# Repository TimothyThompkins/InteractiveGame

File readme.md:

## Description

This is a work in progress, but ultimately aspires to a space invaders-esque game which is played completely on an embedded touch controller and interfaced with a display device such as a computer, or Rasbery Pi.

### Current revision of the PCB:

### The unpopulated (left) and populated (right) boards:

### Loading screen for the game, developed in python:

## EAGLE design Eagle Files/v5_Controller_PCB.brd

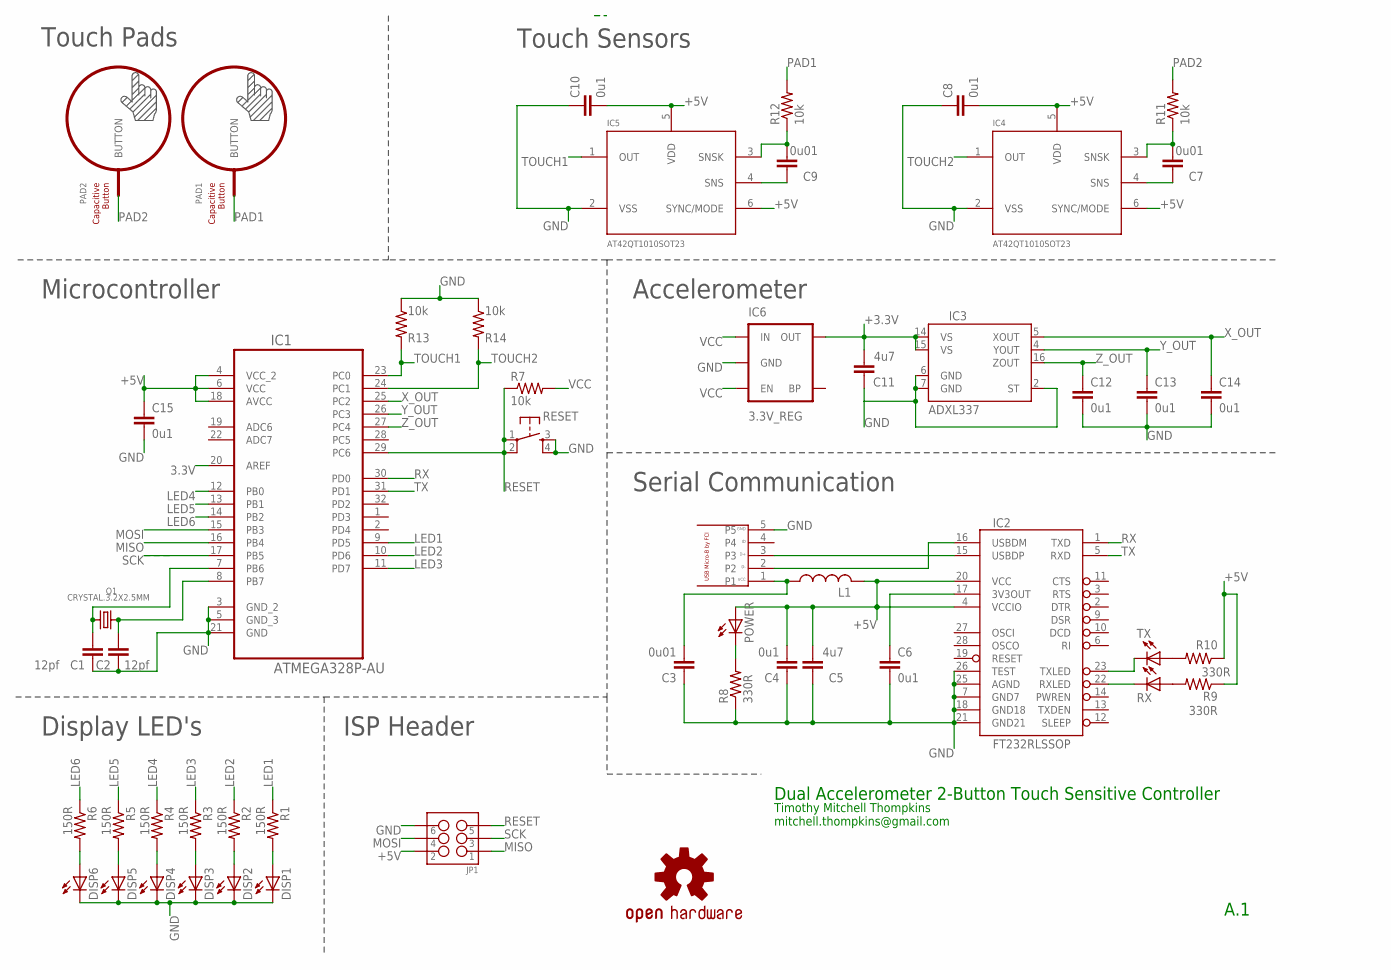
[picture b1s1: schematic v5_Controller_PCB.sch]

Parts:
BUTTON1: TOUCH_LOGO
C1, C2: 12pf; C0603
C3, C7, C9: 0u01; C0603
C4, C6, C8, C10, C12, C13, C14, C15: 0u1; C0603
C5, C11: 4u7; C0603
DISP1, DISP2, DISP3, DISP4, DISP5, DISP6: LEDCHIPLED_0603; CHIPLED_0603
IC1: ATMEGA328P-AU; QFP80P900X900X120-32N
IC2: FT232RLSSOP; SSOP28DB
IC3: ADXL337; LFCSP_LQ-16
IC4, IC5: AT42QT1010SOT23; SOT23-6
IC6: 3.3V_REG; SOT23-5
JP1: M03X2POGO_PINS; 2X3_POGO
L1: L-USL2012C; L2012C
LOGO2: OSHW-LOGOS; OSHW-LOGO-S
PAD1, PAD2: BUTTON_PASSIVE8MM; BUTTON_PASSIVE_8MM
POWER: LEDCHIPLED_0603; CHIPLED_0603
Q1: CRYSTAL.3.2X2.5MM; 3.2X2.5MM
R1, R2, R3, R4, R5, R6: 150R; 0603-RES
R7, R11, R12, R13, R14: 10k; 0603-RES
R8, R9, R10: 330R; 0603-RES
RESET: RESET; TACTILE_SWITCH_SMD
RX: LEDCHIPLED_0603; CHIPLED_0603
TX: LEDCHIPLED_0603; CHIPLED_0603
U$1: USB_MICRO_B_FCI; 10118194-0001LF
U$6: TOUCH_LOGO

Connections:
3.3V: IC1.20 (AREF)
+3.3V: C11.2, IC3.14 (VS), IC3.15 (VS), IC6.5 (OUT)
+5V: C4.2, C5.2, C8.2, C10.2, C15.1, IC1.4 (VCC_2), IC1.6 (VCC), IC1.18 (AVCC), IC2.4 (VCCIO), IC2.20 (VCC), IC4.5 (VDD), IC4.6 (SYNC/MODE), IC5.5 (VDD), IC5.6 (SYNC/MODE), JP1.P$2 (2), L1.2, POWER.A, R9.1, R10.1
GND: C1.1, C2.1, C3.1, C4.1, C5.1, C6.2, C8.1, C10.1, C11.1, C15.2, DISP1.C, DISP2.C, DISP3.C, DISP4.C, DISP5.C, DISP6.C, IC1.3 (GND_2), IC1.5 (GND_3), IC1.21 (GND), IC2.7 (GND7), IC2.18 (GND18), IC2.21 (GND21), IC2.25 (AGND), IC2.26 (TEST), IC3.2 (ST), IC3.6 (GND), IC3.7 (GND), IC4.2 (VSS), IC5.2 (VSS), IC6.2 (GND), JP1.P$6 (6), Q1.2 (GND), Q1.4 (GND), R8.1, R13.1, R14.1, RESET.3, RESET.4, U$1.5, U$1.GND@1 (GND), U$1.GND@2 (GND), U$1.GND@3 (GND), U$1.GND@4 (GND)
LED1: IC1.9 (PD5), R1.1
LED2: IC1.10 (PD6), R2.1
LED3: IC1.11 (PD7), R3.1
LED4: IC1.12 (PB0), R4.1
LED5: IC1.13 (PB1), R5.1
LED6: IC1.14 (PB2), R6.1
MISO: IC1.16 (PB4), JP1.P$1 (1)
MOSI: IC1.15 (PB3), JP1.P$4 (4)
unnamed: C9.2, IC5.3 (SNSK), R12.1
unnamed: C3.2, L1.1, U$1.1
unnamed: C2.2, IC1.8 (PB7), Q1.3
unnamed: C9.1, IC5.4 (SNS)
unnamed: POWER.C, R8.2
unnamed: C1.2, IC1.7 (PB6), Q1.1
unnamed: R10.2, TX.A
unnamed: C6.1, IC2.17 (3V3OUT)
unnamed: R9.2, RX.A
unnamed: IC2.16 (USBDM), U$1.2
unnamed: IC2.15 (USBDP), U$1.3
unnamed: IC2.23 (TXLED), TX.C
unnamed: IC2.22 (RXLED), RX.C
unnamed: C12.2, C13.2, C14.2
unnamed: C7.1, IC4.4 (SNS)
unnamed: C7.2, IC4.3 (SNSK), R11.1
unnamed: DISP1.A, R1.2
unnamed: DISP2.A, R2.2
unnamed: DISP3.A, R3.2
unnamed: DISP4.A, R4.2
unnamed: DISP5.A, R5.2
unnamed: DISP6.A, R6.2
PAD1: PAD1.P$1, R12.2
PAD2: PAD2.P$1, R11.2
RESET: IC1.29 (PC6), JP1.P$5 (5), R7.1, RESET.1, RESET.2
RX: IC1.30 (PD0), IC2.1 (TXD)
SCK: IC1.17 (PB5), JP1.P$3 (3)
TOUCH1: IC1.23 (PC0), IC5.1 (OUT), R13.2
TOUCH2: IC1.24 (PC1), IC4.1 (OUT), R14.2
TX: IC1.31 (PD1), IC2.5 (RXD)
VCC: IC6.1 (IN), IC6.3 (EN), R7.2
X_OUT: C14.1, IC1.25 (PC2), IC3.5 (XOUT)
Y_OUT: C13.1, IC1.26 (PC3), IC3.4 (YOUT)
Z_OUT: C12.1, IC1.27 (PC4), IC3.16 (ZOUT)

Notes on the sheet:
Timothy Mitchell Thompkins mitchell.thompkins@gmail.com
Dual Accelerometer 2-Button Touch Sensitive Controller
A.1
ISP Header
Touch Pads
Touch Sensors
Microcontroller
Serial Communication
Display LED's
Accelerometer

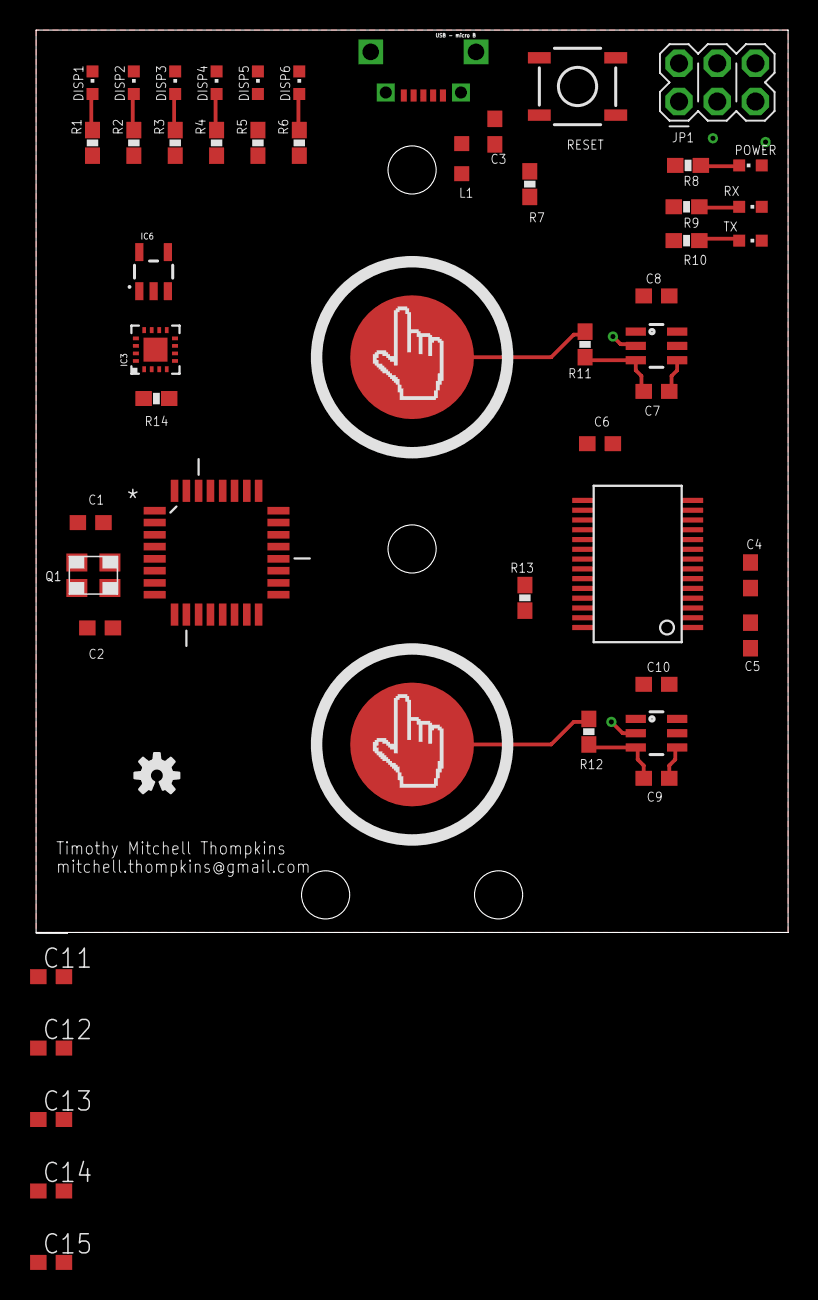
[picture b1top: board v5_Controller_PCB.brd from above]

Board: 2 copper layers, 50.0 x 60.0 mm, 54 parts (0 on the bottom side), 45 nets.

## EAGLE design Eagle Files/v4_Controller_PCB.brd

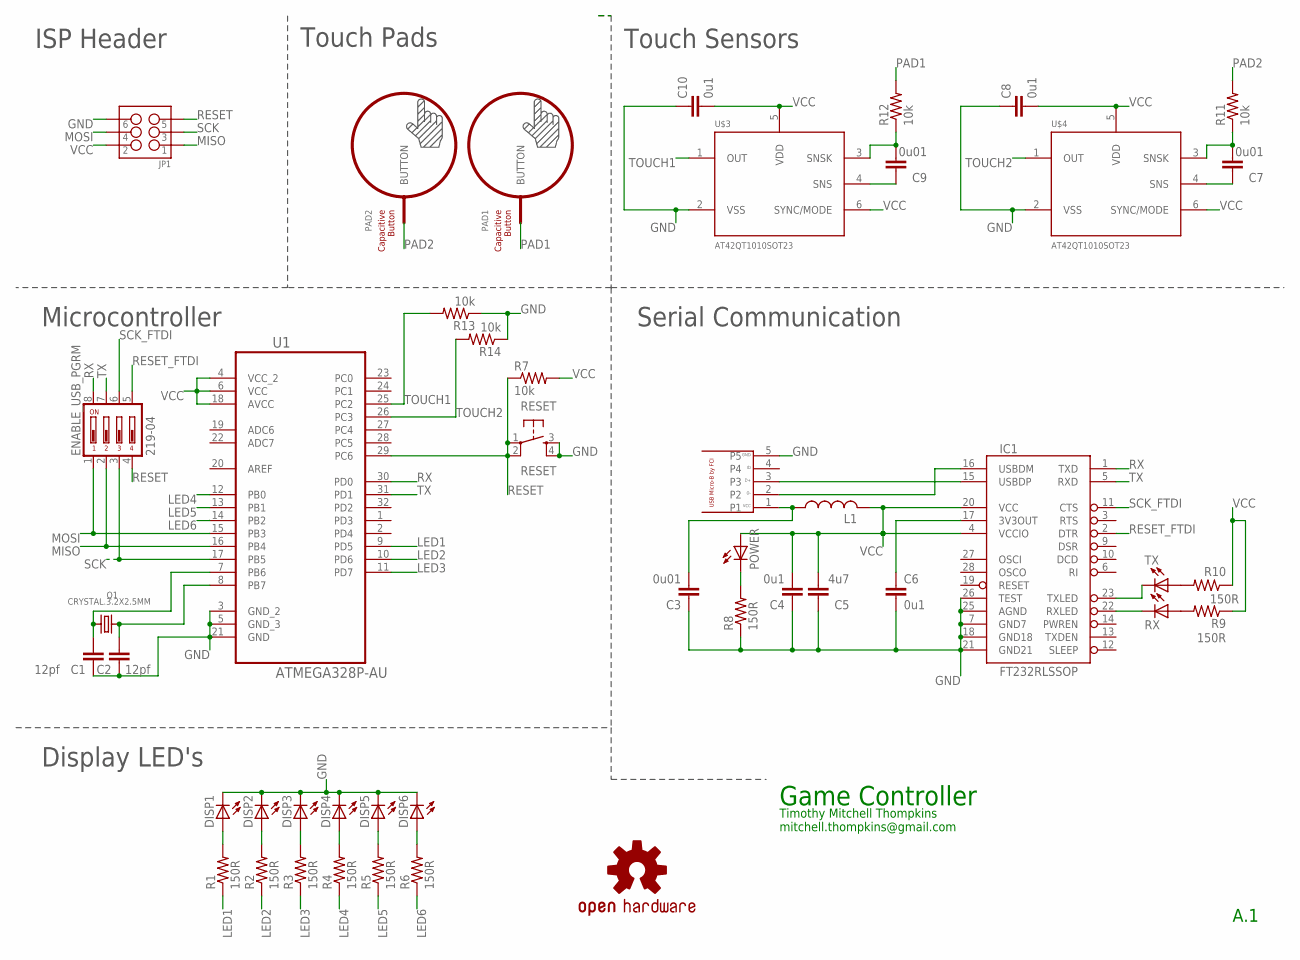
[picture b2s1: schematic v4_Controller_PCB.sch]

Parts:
BUTTON1: TOUCH_LOGO
C1, C2: 12pf; C0603
C3, C7, C9: 0u01; C0603
C4, C6, C8, C10: 0u1; C0603
C5: 4u7; C0603
DISP1, DISP2, DISP3, DISP4, DISP5, DISP6: LEDCHIPLED_0603; CHIPLED_0603
ENABLE_USB_PGRM: 219-04; CTS-219-04
IC1: FT232RLSSOP; SSOP28DB
JP1: M03X2POGO_PINS; 2X3_POGO
L1: L-USL2012C; L2012C
LOGO2: OSHW-LOGOS; OSHW-LOGO-S
PAD1, PAD2: BUTTON_PASSIVE8MM; BUTTON_PASSIVE_8MM
POWER: LEDCHIPLED_0603; CHIPLED_0603
Q1: CRYSTAL.3.2X2.5MM; 3.2X2.5MM
R1, R2, R3, R4, R5, R6, R8, R9, R10: 150R; 0603-RES
R7, R11, R12, R13, R14: 10k; 0603-RES
RESET: RESET; TACTILE-PTH
RX: LEDCHIPLED_0603; CHIPLED_0603
TX: LEDCHIPLED_0603; CHIPLED_0603
U1: ATMEGA328P-AU; QFP80P900X900X120-32N
U$1: USB_MICRO_B_FCI; 10118194-0001LF
U$3, U$4: AT42QT1010SOT23; SOT23-6
U$6: TOUCH_LOGO

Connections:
GND: C1.1, C2.1, C3.1, C4.1, C5.1, C6.2, C8.1, C10.1, DISP1.C, DISP2.C, DISP3.C, DISP4.C, DISP5.C, DISP6.C, IC1.7 (GND7), IC1.18 (GND18), IC1.21 (GND21), IC1.25 (AGND), IC1.26 (TEST), JP1.P$6 (6), Q1.2 (GND), Q1.4 (GND), R8.1, R13.1, R14.1, RESET.3, RESET.4, U1.3 (GND_2), U1.5 (GND_3), U1.21 (GND), U$1.5, U$1.GND@1 (GND), U$1.GND@2 (GND), U$1.GND@3 (GND), U$1.GND@4 (GND), U$3.2 (VSS), U$4.2 (VSS)
LED1: R1.1, U1.9 (PD5)
LED2: R2.1, U1.10 (PD6)
LED3: R3.1, U1.11 (PD7)
LED4: R4.1, U1.12 (PB0)
LED5: R5.1, U1.13 (PB1)
LED6: R6.1, U1.14 (PB2)
MISO: ENABLE_USB_PGRM.2, JP1.P$1 (1), U1.16 (PB4)
MOSI: ENABLE_USB_PGRM.1, JP1.P$4 (4), U1.15 (PB3)
unnamed: C9.2, R12.1, U$3.3 (SNSK)
unnamed: C3.2, L1.1, U$1.1
unnamed: C2.2, Q1.3, U1.8 (PB7)
unnamed: C9.1, U$3.4 (SNS)
unnamed: POWER.C, R8.2
unnamed: C1.2, Q1.1, U1.7 (PB6)
unnamed: R10.2, TX.A
unnamed: C6.1, IC1.17 (3V3OUT)
unnamed: R9.2, RX.A
unnamed: IC1.16 (USBDM), U$1.2
unnamed: IC1.15 (USBDP), U$1.3
unnamed: IC1.23 (TXLED), TX.C
unnamed: IC1.22 (RXLED), RX.C
unnamed: C7.1, U$4.4 (SNS)
unnamed: C7.2, R11.1, U$4.3 (SNSK)
unnamed: DISP1.A, R1.2
unnamed: DISP2.A, R2.2
unnamed: DISP3.A, R3.2
unnamed: DISP4.A, R4.2
unnamed: DISP5.A, R5.2
unnamed: DISP6.A, R6.2
PAD1: PAD1.P$1, R12.2
PAD2: PAD2.P$1, R11.2
RESET: ENABLE_USB_PGRM.4, JP1.P$5 (5), R7.1, RESET.1, RESET.2, U1.29 (PC6)
RESET_FTDI: ENABLE_USB_PGRM.5, IC1.2 (DTR)
RX: ENABLE_USB_PGRM.8, IC1.1 (TXD), U1.30 (PD0)
SCK: ENABLE_USB_PGRM.3, JP1.P$3 (3), U1.17 (PB5)
SCK_FTDI: ENABLE_USB_PGRM.6, IC1.11 (CTS)
TOUCH1: R13.2, U1.25 (PC2), U$3.1 (OUT)
TOUCH2: R14.2, U1.26 (PC3), U$4.1 (OUT)
TX: ENABLE_USB_PGRM.7, IC1.5 (RXD), U1.31 (PD1)
VCC: C4.2, C5.2, C8.2, C10.2, IC1.4 (VCCIO), IC1.20 (VCC), JP1.P$2 (2), L1.2, POWER.A, R7.2, R9.1, R10.1, U1.4 (VCC_2), U1.6 (VCC), U1.18 (AVCC), U$3.5 (VDD), U$3.6 (SYNC/MODE), U$4.5 (VDD), U$4.6 (SYNC/MODE)

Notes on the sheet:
Timothy Mitchell Thompkins mitchell.thompkins@gmail.com
Game Controller
A.1
ISP Header
Touch Pads
Touch Sensors
Microcontroller
Serial Communication
Display LED's

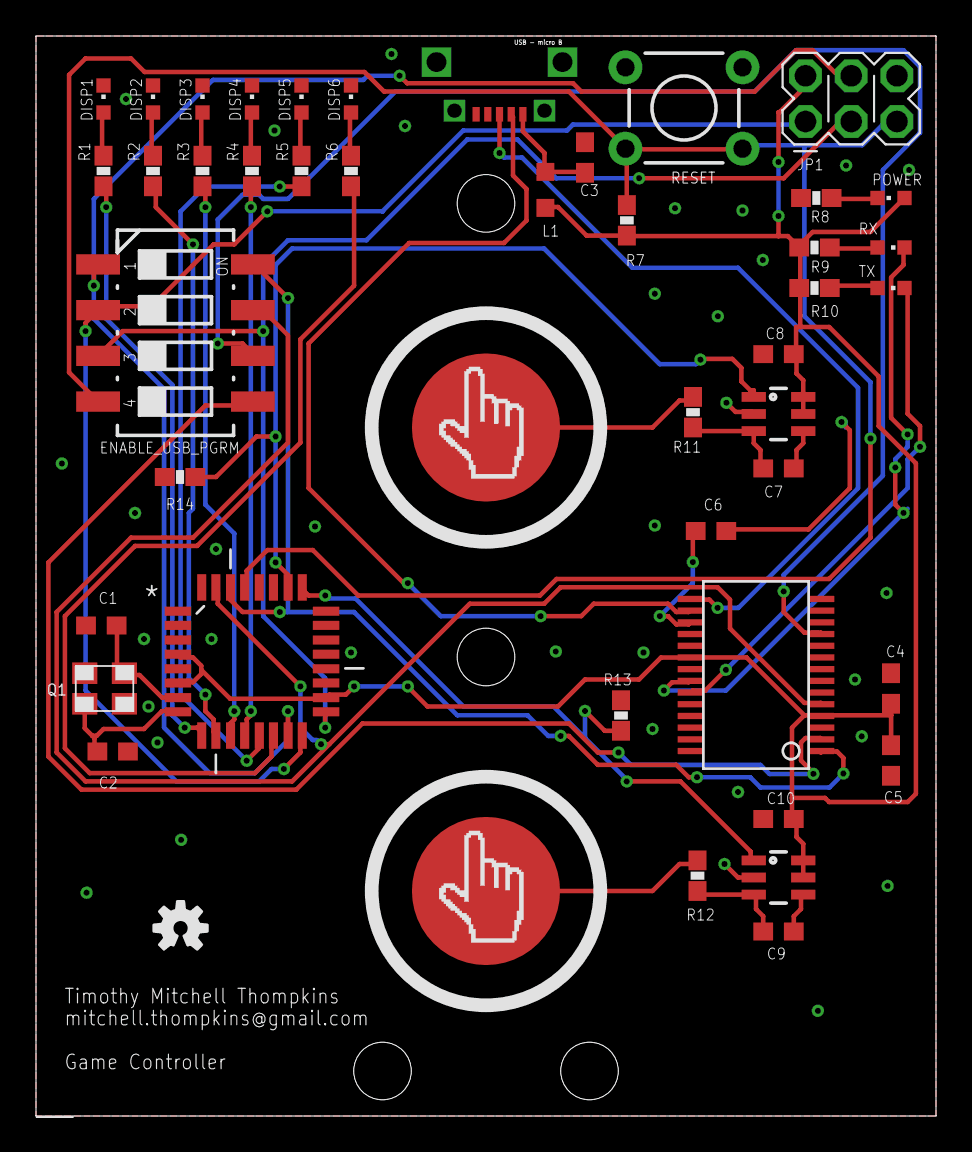
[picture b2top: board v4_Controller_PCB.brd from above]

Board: 2 copper layers, 50.0 x 60.0 mm, 48 parts (0 on the bottom side), 41 nets.

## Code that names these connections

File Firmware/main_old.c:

/*
* Hello_World.c
*
* Created: 9/28/2014 1:23:27 PM
*  Author: TimothyThompkins
*/

#define F_CPU 20000000UL // 20MHz

#include <avr/delay.h>
#include <avr/io.h>
#include <avr/interrupt.h>

#define 	UCSRA 	UCSR0A
#define 	UCSRB 	UCSR0B
#define 	UCSRC 	UCSR0C
#define 	UBRRH 	UBRR0H
#define 	UBRRL 	UBRR0L
#define 	UDRE 	UDRE0
#define 	UDR 		UDR0
#define 	RXC 		RXC0
#define TXEN		TXEN0
#define RXEN		RXEN0
#define RXCIE	RXCIE0

// Define baud rate
#define USART_BAUDRATE 9600
#define BAUD_PRESCALE (((F_CPU / (USART_BAUDRATE * 16UL))) - 1)

// Define baud rate 9600 is a safe speed as it is fast enough for most things we will use this speed
#define USART_BAUDRATE 9600

// Define the prescaler to use. This is based on the clock speed the AVR is running
#define BAUD_PRESCALE (((F_CPU / (USART_BAUDRATE * 16UL))) - 1)

void USART_Init(void){
	/*
	First set the BAUD rate, because this register is actually more than 8 bits
	we need to load the lower 8 bits and upper 8 bits independently from one another.
	We will load the lower 8 bits first and upper 8 bits after.
	Also the default frame format is 8 data bits, no parity and 1 stopbit (also known as 8n1))
	We will use this format so no change needed here
	*/
	UBRRL = BAUD_PRESCALE; // Load lower 8 bits
	UBRRH = (BAUD_PRESCALE >> 8); // Load upper 8 bits
	// Enable transmitter only
	// UCSRB = 1<<TXEN;
	UCSRB =(1<<RXEN0)|(1<<TXEN0);

}

void USART_SendByte(uint8_t data){

	// Wait until last byte has been transmitted
	while((UCSRA &(1<<UDRE)) == 0);

	// Transmit data
	UDR = data;
}

USART_ReceiveByte(){
	while ((UCSRA & (1 << RXC)) == 0);
	// Do nothing until data has been received and is ready to be read from UDR
	return(UDR); // return the byte
}

//volatile unsigned char value;
/* This variable is volatile so both main and RX interrupt can use it.
It could also be a uint8_t type */

/* Interrupt Service Routine for Receive Complete
NOTE: vector name changes with different AVRs see AVRStudio -
Help - AVR-Libc reference - Library Reference - <avr/interrupt.h>: Interrupts
for vector names other than USART_RXC_vect for ATmega32 */
/*
ISR(USART_RX_vect){

value = UDR;             //read UART register into value
PORTB = ~value;          // output inverted value on LEDs (0=on)
}

void USART_Init(void){
// Set baud rate
UBRRL = BAUD_PRESCALE;// Load lower 8-bits into the low byte of the UBRR register
UBRRH = (BAUD_PRESCALE >> 8);
Load upper 8-bits into the high byte of the UBRR register
Default frame format is 8 data bits, no parity, 1 stop bit
to change use UCSRC, see AVR datasheet

// Enable receiver and transmitter and receive complete interrupt
UCSRB = ((1<<TXEN)|(1<<RXEN) | (1<<RXCIE));
}


void USART_SendByte(uint8_t u8Data){

// Wait until last byte has been transmitted
while((UCSRA &(1<<UDRE)) == 0);

// Transmit data
UDR = u8Data;
}


// not being used but here for completeness
// Wait until a byte has been received and return received data
uint8_t USART_ReceiveByte(){
while((UCSRA &(1<<RXC)) == 0);
return UDR;
}
*/

int main(void)
{

	uint8_t data;
	USART_Init();  // Initialise USART
	//sei();         // enable all interrupts
	char value = 'U'; //0x41;

	//Pin I/O Definitions
	DDRB = 0b00000111;
	DDRC = 0b00000000;
	DDRD = 0b11100000;

	while(1)
	{
		//This is a hello world the LED's
		// for (uint8_t i = 5; i<=7; i++)
		// { //Start at 5 b/c the first LED is connected to PD5
		// PORTD ^= 1<<i;
		// _delay_ms(1000);//This is a 20ms delay
		// }

		// for (uint8_t i = 0; i<=2; i++)
		// {
		// PORTB ^= 1<<i;
		// _delay_ms(1000);//This is a 20ms delay
		// }

		USART_SendByte(value);  // send value
		data = USART_ReceiveByte();

		if (data == 'U')
		{
			USART_SendByte('T');  // Send value
			_delay_ms(100);
		}

		else
		{
			USART_SendByte('N');  // Send value
			_delay_ms(100);
		}

		if (PINC & (1<<PC2))
		{
			PORTD |= (1<<PD5);
		}
		else
		{
			PORTD &= ~(1<<PD5);
		}

		if (PINC & (1<<PC3))
		{
			PORTD |= (1<<PD6);
		}
		else
		{
			PORTD &= ~(1<<PD6);
		}
	}
}

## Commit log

2015-03-23 fixed untracked files
2015-03-23 Maybe now
2015-03-23 Removed .DS_Store
2015-03-23 Going Home
2015-03-23 Added main.c and Makefile
2015-03-23 Updated Gitignore. Added Test/ to computer
2015-03-23 Testing
2015-03-23 Changed LED Test Pins
2015-03-28 Some c++ serial testing
2015-03-29 Got Basic Serial Working with Atmega1284P
2015-03-30 Got test serial python working
2015-04-01 Started Defining Game
2015-04-05 Python windows
2015-04-06 Developing on linux
2015-04-06 Got some window stuff working
2015-04-06 Got window resizing working
2015-04-07 Basic Start Window Working
2015-04-07 Trying to get event binding working
2015-04-07 Removed Old Files
2015-04-07 Got some stuff working
2015-04-08 Just made some slight changes. mostly research
2015-04-09 test
2015-04-12 Yo B why this in't workn?
2015-04-14 Adding serial comms
2015-04-15 Nothing Big
2015-04-26 Got menu selection working
2015-04-27 Trying to pass game parameters to main.py
2015-04-27 Start Error Handling. Argument Passing working
2015-04-27 Added errors file
2015-04-27 Error Message working. Minus Image
2015-04-28 Got error message correct and window cleaned up.
2015-04-30 Gearing up to start comms. Linux verison buggy
2015-04-30 Added some Linux Support
2015-04-30 Fixed some dumb linux vs OSX bull
2015-05-01 Overhauling Circuit Diagram
2015-05-05 Cleaned up Python Folder
2015-05-05 On the verge of getting init sequence to communicate properly
2015-05-06 Trying to figure out ISR & return char array on avr
2015-05-10 Not Functional
2015-08-03 Getting back into it.
2015-08-10 Serial Comms Are Working
2015-08-10 Cleaned up Serial. Changed names
2015-08-10 Cleaned up Serial. Changed filenames
2015-08-14 Playing with pyserial on OSX
2015-08-14 PYSERIAL WHY YOU NO WORK!?!
2016-03-17 Added Readme
2016-03-17 Modifed 1284p test firmware
2016-04-04 Added Pictures
2016-04-04 Modified Readme

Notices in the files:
parts and their libraries:
SparkFun: Licensing: CC v3.0 Share-Alike You are welcome to use this library for commercial purposes.
PatternAgents-TouchWidgets: License : http://creativecommons.org/licenses/by-sa/4.0/ (Creative Commons 4.0)
